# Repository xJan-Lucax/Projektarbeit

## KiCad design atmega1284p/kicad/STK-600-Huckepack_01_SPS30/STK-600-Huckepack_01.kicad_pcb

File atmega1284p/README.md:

[[_TOC_]]

# Projektarbeit - Mikrocontroller Atmega1284P

# Datenblätter

[Atmega16](https://ww1.microchip.com/downloads/en/devicedoc/doc2466.pdf)

[Atmega1284P](https://ww1.microchip.com/downloads/en/DeviceDoc/doc8059.pdf)

[STK600](http://ww1.microchip.com/downloads/en/devicedoc/40001904a.pdf)

[ILI9341](https://www.roboter-bausatz.de/media/pdf/df/61/ee/An-Display-3.pdf)

# Prüfliste

- [x] Falscher Mikrocontroller auf STK (#ifndef ATmega16)
- [x] LED Library
- [x] LED + Portierung 
- [x] Single Slave 
    1. - [x] LED Reihenfolge + 3-bit Counter
- [x] Multi Slave 
- [x] Buffer Priortiy Queue
- [x] RFM95 SPI 
- [x] Display SPI 
- [x] USART zum Debuggen

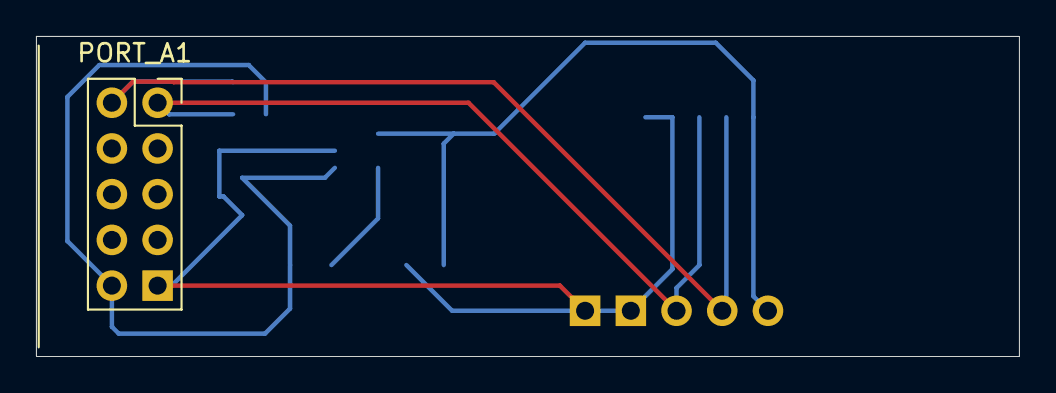
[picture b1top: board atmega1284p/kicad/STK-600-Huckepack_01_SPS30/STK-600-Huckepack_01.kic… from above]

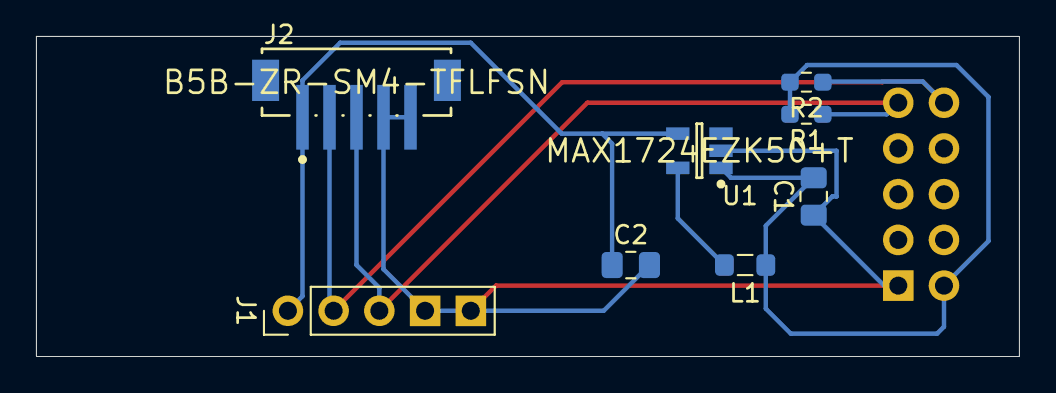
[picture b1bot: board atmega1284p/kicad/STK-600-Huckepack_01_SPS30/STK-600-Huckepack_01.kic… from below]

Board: 2 copper layers, 54.6 x 17.8 mm, 9 parts (8 on the bottom side), 6 nets.

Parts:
C1, C2: C; C_0805_2012Metric_Pad1.18x1.45mm_HandSolder
J1: Conn_01x05_Male; PinHeader_1x05_P2.54mm_Vertical
J2: B5B-ZR-SM4-TFLFSN; JST-B5B-ZR-SM4-TF
L1: L; L_0805_2012Metric_Pad1.05x1.20mm_HandSolder
PORT_A1: Conn_02x05_Odd_Even_MountingPin; PinSocket_2x05_P2.54mm_Vertical
R1, R2: R; R_0603_1608Metric_Pad0.98x0.95mm_HandSolder
U1: MAX1724EZK50+T; Maxim-MAX1724EZK50+T-Level_A

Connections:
/GND: C1.1, C2.2, J1.4, J1.5, J2.4, J2.5, PORT_A1.9, U1.2
/SCL: J1.3, J2.3, PORT_A1.1, R1.1
/SDA: J1.2, J2.2, PORT_A1.2, R2.1
/VCC: C1.2, L1.1, PORT_A1.10, R1.2, R2.2, U1.1, U1.3
unnamed: C2.1, J1.1, J2.1, U1.4
unnamed: L1.2, U1.5

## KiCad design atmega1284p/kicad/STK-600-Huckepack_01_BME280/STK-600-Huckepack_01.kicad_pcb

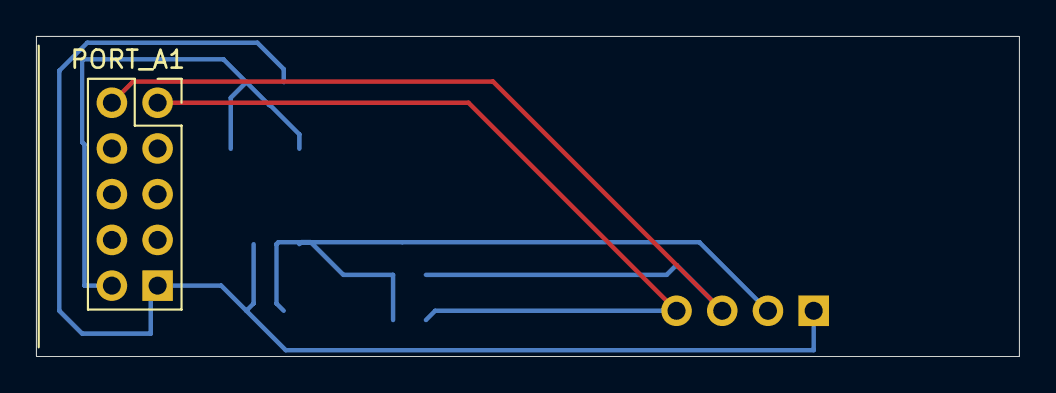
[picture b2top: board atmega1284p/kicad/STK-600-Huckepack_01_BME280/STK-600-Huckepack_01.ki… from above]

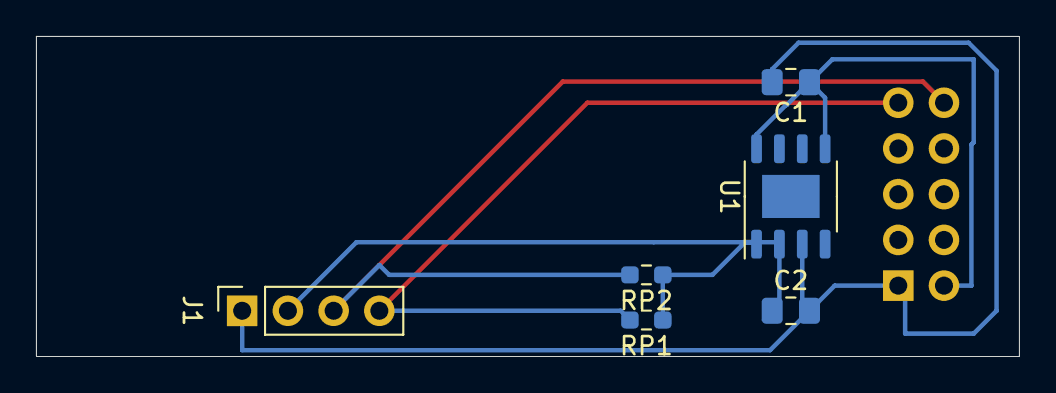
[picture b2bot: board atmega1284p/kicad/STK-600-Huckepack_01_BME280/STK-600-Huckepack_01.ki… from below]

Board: 2 copper layers, 54.6 x 17.8 mm, 7 parts (6 on the bottom side), 5 nets.

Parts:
C1, C2: C; C_0805_2012Metric_Pad1.18x1.45mm_HandSolder
J1: Conn_01x04_Male; PinSocket_1x04_P2.54mm_Vertical
PORT_A1: Conn_02x05_Odd_Even_MountingPin; PinSocket_2x05_P2.54mm_Vertical
RP1, RP2: R; R_0603_1608Metric_Pad0.98x0.95mm_HandSolder
U1: BD33GA5WEFJ; HTSOP-8-1EP_3.9x4.9mm_P1.27mm_EP2.4x3.2mm

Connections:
/GND: C1.2, C2.2, J1.1, PORT_A1.9, U1.3, U1.4, U1.6, U1.7, U1.9
/SCL: J1.4, PORT_A1.1, RP1.2
/SDA: J1.3, PORT_A1.2, RP2.2
/VCC: C1.1, PORT_A1.10, U1.5, U1.8
/VCC-3,3V: C2.1, J1.2, RP1.1, RP2.1, U1.1, U1.2

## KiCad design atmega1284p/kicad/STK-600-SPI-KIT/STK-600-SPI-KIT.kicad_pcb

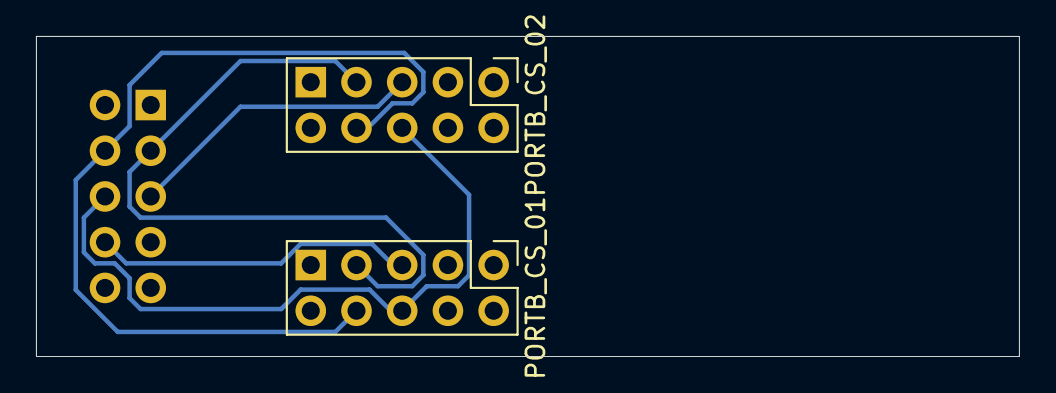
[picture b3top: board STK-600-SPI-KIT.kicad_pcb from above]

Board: 2 copper layers, 54.6 x 17.8 mm, 3 parts (1 on the bottom side), 5 nets.

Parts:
PORTB_CS_01, PORTB_CS_02: Conn_02x05_Odd_Even; PinHeader_2x05_P2.54mm_Vertical
PORT_B1: Conn_02x05_Odd_Even; PinSocket_2x05_P2.54mm_Vertical

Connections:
unnamed: PORTB_CS_01.5, PORT_B1.4
unnamed: PORTB_CS_01.6, PORTB_CS_02.6, PORT_B1.6
unnamed: PORTB_CS_01.7, PORTB_CS_02.7, PORT_B1.7
unnamed: PORTB_CS_01.8, PORTB_CS_02.8, PORT_B1.8
unnamed: PORTB_CS_02.5, PORT_B1.5

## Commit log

2023-04-12 Upload
    Main
2023-04-12 Debug functions
    Debug
